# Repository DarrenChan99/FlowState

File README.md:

# PlantVision
Plant Vision is a data driven project that aims to use onboard sensors to display useful information and warnings to the user like a predictive watering algorithm and CO2 threshold monitor to help optimally track and water plants and improve productivity through elevated CO2 level warnings, signaling to the user it might be time to step outside.   

# Why?
Recently one of my plants died to unknown factors and I realized that I was guessing when to water and how much sun to give it. At this same time I was getting into C++, microcontrollers, and data based algorithms to build my skills. So after some brainstorming this project perfectly encapsulated my needs while providing a hardware challenge with the custom PCB and an open software ceiling where I could explore data algorithms like the low pass filter and predictive irrigation and experiment with python to better visulize the data and show it on the LCD. 

### Gallery

#### Schematic

#### PCB Layout

#### 3D Render

#### CAD View (Front)

#### CAD View (Back)

## BOM
| Component | Description | Part Number | Source | Qty | Notes |
| :--- | :--- | :--- | :--- | :--- | :--- |
| **USB-C** | 16-pin (USB 2.0), Top Mount, Right Angle | **USB4105-GF-A** | DigiKey | 1 | Exact match for HRO footprint. 5A Rated. |
| **CO2 / Temp / Hum** | Sensirion SCD41 Photoacoustic Sensor | **SCD41** | AliExpress | 1 | High accuracy air quality sensing (I2C). |
| **Microcontroller** | ESP32 DevKit V1 (Narrow 30-Pin) | **ESP-WROOM-32** | Amazon | 1 | Dual-core processor with Wi-Fi/Bluetooth. |
| **Voltage Regulator** | 3.3V 800mA LDO (TO-220) | **LD1117V33** | DigiKey | 1 | Converts 5V USB power to 3.3V. |
| **Input Cap (C1)** | 10µF 25V Electrolytic Radial | **860020472003** | DigiKey | 1 | Bulk filter for 5V rail (Würth ATG5). |
| **Output Cap (C2)** | 47µF 16V Electrolytic Radial | **860010372004** | DigiKey | 1 | Stabilizes 3.3V rail (Würth ATG8). |
| **Bypass Cap (C3)** | 100nF 50V X7R Ceramic Radial | **K104K10X7RF5UH5**| DigiKey | 1 | High-frequency noise filter (Vishay). |
| **Resistors** | 5.1k Ohm 1/4W 1% Metal Film | **MFR-25FTE52-5K1**| DigiKey | 2 | Required for SDA/SCL data stability. |
| **Soil Sensor** | Capacitive Moisture Sensor v1.2 | **Generic** | Amazon | 1 | Corrosion-resistant soil tracking. |
| **LCD Touchscreen** | 2.8" or 3.5" TFT SPI Display | **ILI9341** | Amazon | 1 | User interface and data visualization. |
| **Solder Wire** | 0.6mm 63/37 Rosin Core | **Generic** | Amazon | 1 | Precision gauge for USB-C soldering. |
| **Custom PCB** | 1.6mm thick, 2 layer | **Generic** | JLPCB | 1 | Wiring |

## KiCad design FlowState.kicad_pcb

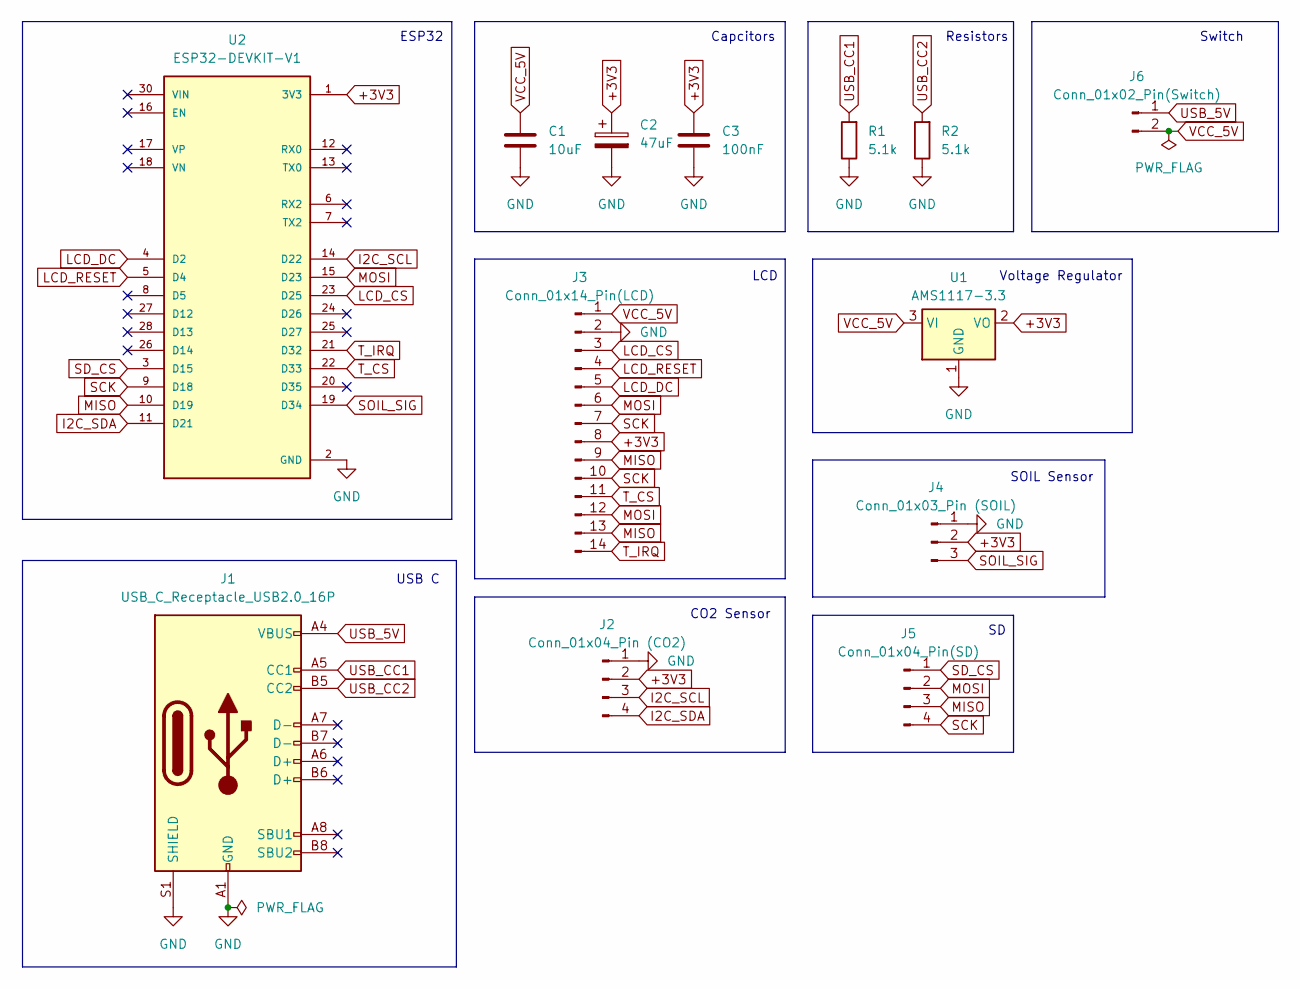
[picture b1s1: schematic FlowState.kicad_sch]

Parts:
C1: 10uF; CP_Radial_D5.0mm_P2.00mm
C2: 47uF; CP_Radial_D5.0mm_P2.00mm
C3: 100nF; C_Disc_D3.0mm_W1.6mm_P2.50mm
J1: USB_C_Receptacle_USB2.0_16P; USB_C_Receptacle_HRO_TYPE-C-31-M-12
J2: Conn_01x04_Pin (CO2); PinHeader_1x04_P2.54mm_Vertical
J3: Conn_01x14_Pin(LCD); PinHeader_1x14_P2.54mm_Vertical
J4: Conn_01x03_Pin (SOIL); PinHeader_1x03_P2.54mm_Vertical
J5: Conn_01x04_Pin(SD); PinHeader_1x04_P2.54mm_Vertical
J6: Conn_01x02_Pin(Switch); PinHeader_1x02_P2.54mm_Vertical
R1, R2: 5.1k; R_Axial_DIN0207_L6.3mm_D2.5mm_P7.62mm_Horizontal
U1: AMS1117-3.3; SOT-223-3_TabPin2
U2: ESP32-DEVKIT-V1; MODULE_ESP32_DEVKIT_V1; PARTREV N/A

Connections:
+3V3: C2.1, C3.1, J2.2, J3.8, J4.2, U1.2 (VO), U2.1 (3V3)
GND: C1.2, C2.2, C3.2, J1.A1 (GND), J1.A12 (GND), J1.B1 (GND), J1.B12 (GND), J1.S1 (SHIELD), J2.1, J3.2, J4.1, R1.1, R2.1, U1.1 (GND), U2.2 (GND), U2.29 (GND)
I2C_SCL: J2.3, U2.14 (D22)
I2C_SDA: J2.4, U2.11 (D21)
LCD_CS: J3.3, U2.23 (D25)
LCD_DC: J3.5, U2.4 (D2)
LCD_RESET: J3.4, U2.5 (D4)
MISO: J3.9, J3.13, J5.3, U2.10 (D19)
MOSI: J3.6, J3.12, J5.2, U2.15 (D23)
SCK: J3.7, J3.10, J5.4, U2.9 (D18)
SD_CS: J5.1, U2.3 (D15)
SOIL_SIG: J4.3, U2.19 (D34)
T_CS: J3.11, U2.22 (D33)
T_IRQ: J3.14, U2.21 (D32)
USB_5V: J1.A4 (VBUS), J1.A9 (VBUS), J1.B4 (VBUS), J1.B9 (VBUS), J6.1; also elsewhere on the board
USB_CC1: J1.A5 (CC1), R1.2
USB_CC2: J1.B5 (CC2), R2.2
VCC_5V: C1.1, J3.1, J6.2, U1.3 (VI); also elsewhere on the board

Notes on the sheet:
ESP32
CO2 Sensor
Voltage Regulator
LCD
SOIL Sensor
Switch
Resistors
Capcitors
USB C

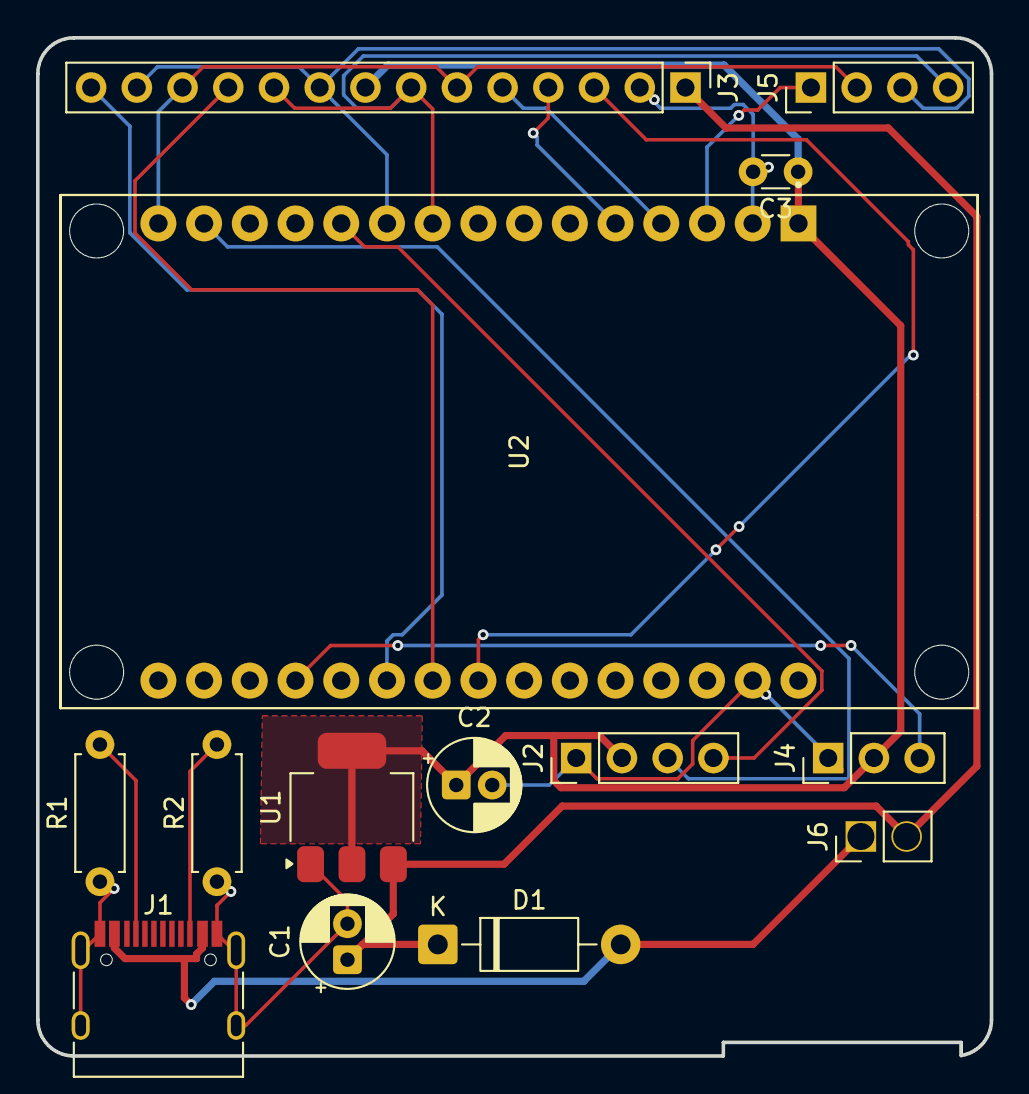
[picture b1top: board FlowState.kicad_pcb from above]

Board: 2 copper layers, 53.0 x 56.6 mm, 14 parts (0 on the bottom side), 18 nets.

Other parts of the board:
D1: 1N5819; D_DO-41_SOD81_P10.16mm_Horizontal

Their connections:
USB_5V: D1.2 (A); also elsewhere on the board
VCC_5V: D1.1 (K); also elsewhere on the board

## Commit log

2026-05-06 added files and gitignore
2026-05-06 fixed git ignore
2026-05-06 Fix: Stop tracking ignored files
2026-05-06 fixed actually
2026-05-06 added more
2026-05-06 fixed?
2026-05-06 fixed ds store to global ignore
2026-05-06 forgot to add:
2026-05-06 edits
    rewired LCD to differnt GPIO because that pin has HIGH voltage at startup
2026-05-07 heatsink
    heatsink good now
2026-05-12 gerber, step, readme
    did lots of stuff
2026-05-12 moved and organized
    moved and organized
2026-05-12 testing
    testing
2026-05-12 readme
2026-05-12 Update .gitignore to exclude more files
    Added additional Gerber files and VSCode configurations to .gitignore.
2026-05-12 chore: sync repo and update gitignore logic
2026-05-12 added code
2026-05-12 removed files
